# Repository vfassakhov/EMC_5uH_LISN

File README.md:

# 5µH LISN(Line Impedance Stabilization Network)

Open Source Hardware Dual 5µH DC LISN with 10dB Attenuator and Transient Limiter for Spectrum Analyzer EMC work.

A LISN is a [Line Impedance Stabilization Network](https://en.wikipedia.org/wiki/Line_Impedance_Stabilization_Network) used in conducted emissions testing.

The AIM of this Dual LISN is to be used for EMC pre-testing with frequency range 30kHz(or lower) to 110MHz(or up to 150MHz or more).

Fork from the [original project](https://github.com/bvernoux/EMC_5uH_LISN), the main changes are made the following:

* Convert project to [KiCad 8.0](https://www.kicad.org) version
* Added [KiBot](https://github.com/INTI-CMNB/KiBot) configuration, for automated generation of the documentation
* Improvement in this design: 
  * Replace Keystone 575-8 by screwed type Chinese alternative
  * Inductors are replaced by more affordable (need to make some tests)
  * BOM changes for cheaper Chinese alternatives
  * Another case (Gainta) is chosen

This work is heavily based on work from others mainly **Jay_Diddy_B** & **Noy** from EEVBLOG forum.

See all links related to the original Dual 5µH LISN:
* https://www.eevblog.com/forum/projects/5uh-lisn-for-spectrum-analyzer-emcemi-work/75/
* https://www.eevblog.com/forum/projects/5uh-lisn-for-spectrum-analyzer-emcemi-work/msg3420102/#msg3420102

Video related to EMC Conducted Emissions / LISN:
* Rohde Schwarz video Understanding LISNs: 
  * This video explains the design and function of a LISN (line impedance stabilization network) and how LISNs are used in conducted EMC testing.
  * https://www.youtube.com/watch?v=QPJzp66Yvzs
* EMC Conducted Emissions: How to connect and set up a LISN:
  * In this video Dr. Ali Shirsavar shows how you can connect and set up a LISN ready for pre-compliance testing of EMC conducted emissions.
  * https://www.youtube.com/watch?v=28oDdL9RnWM

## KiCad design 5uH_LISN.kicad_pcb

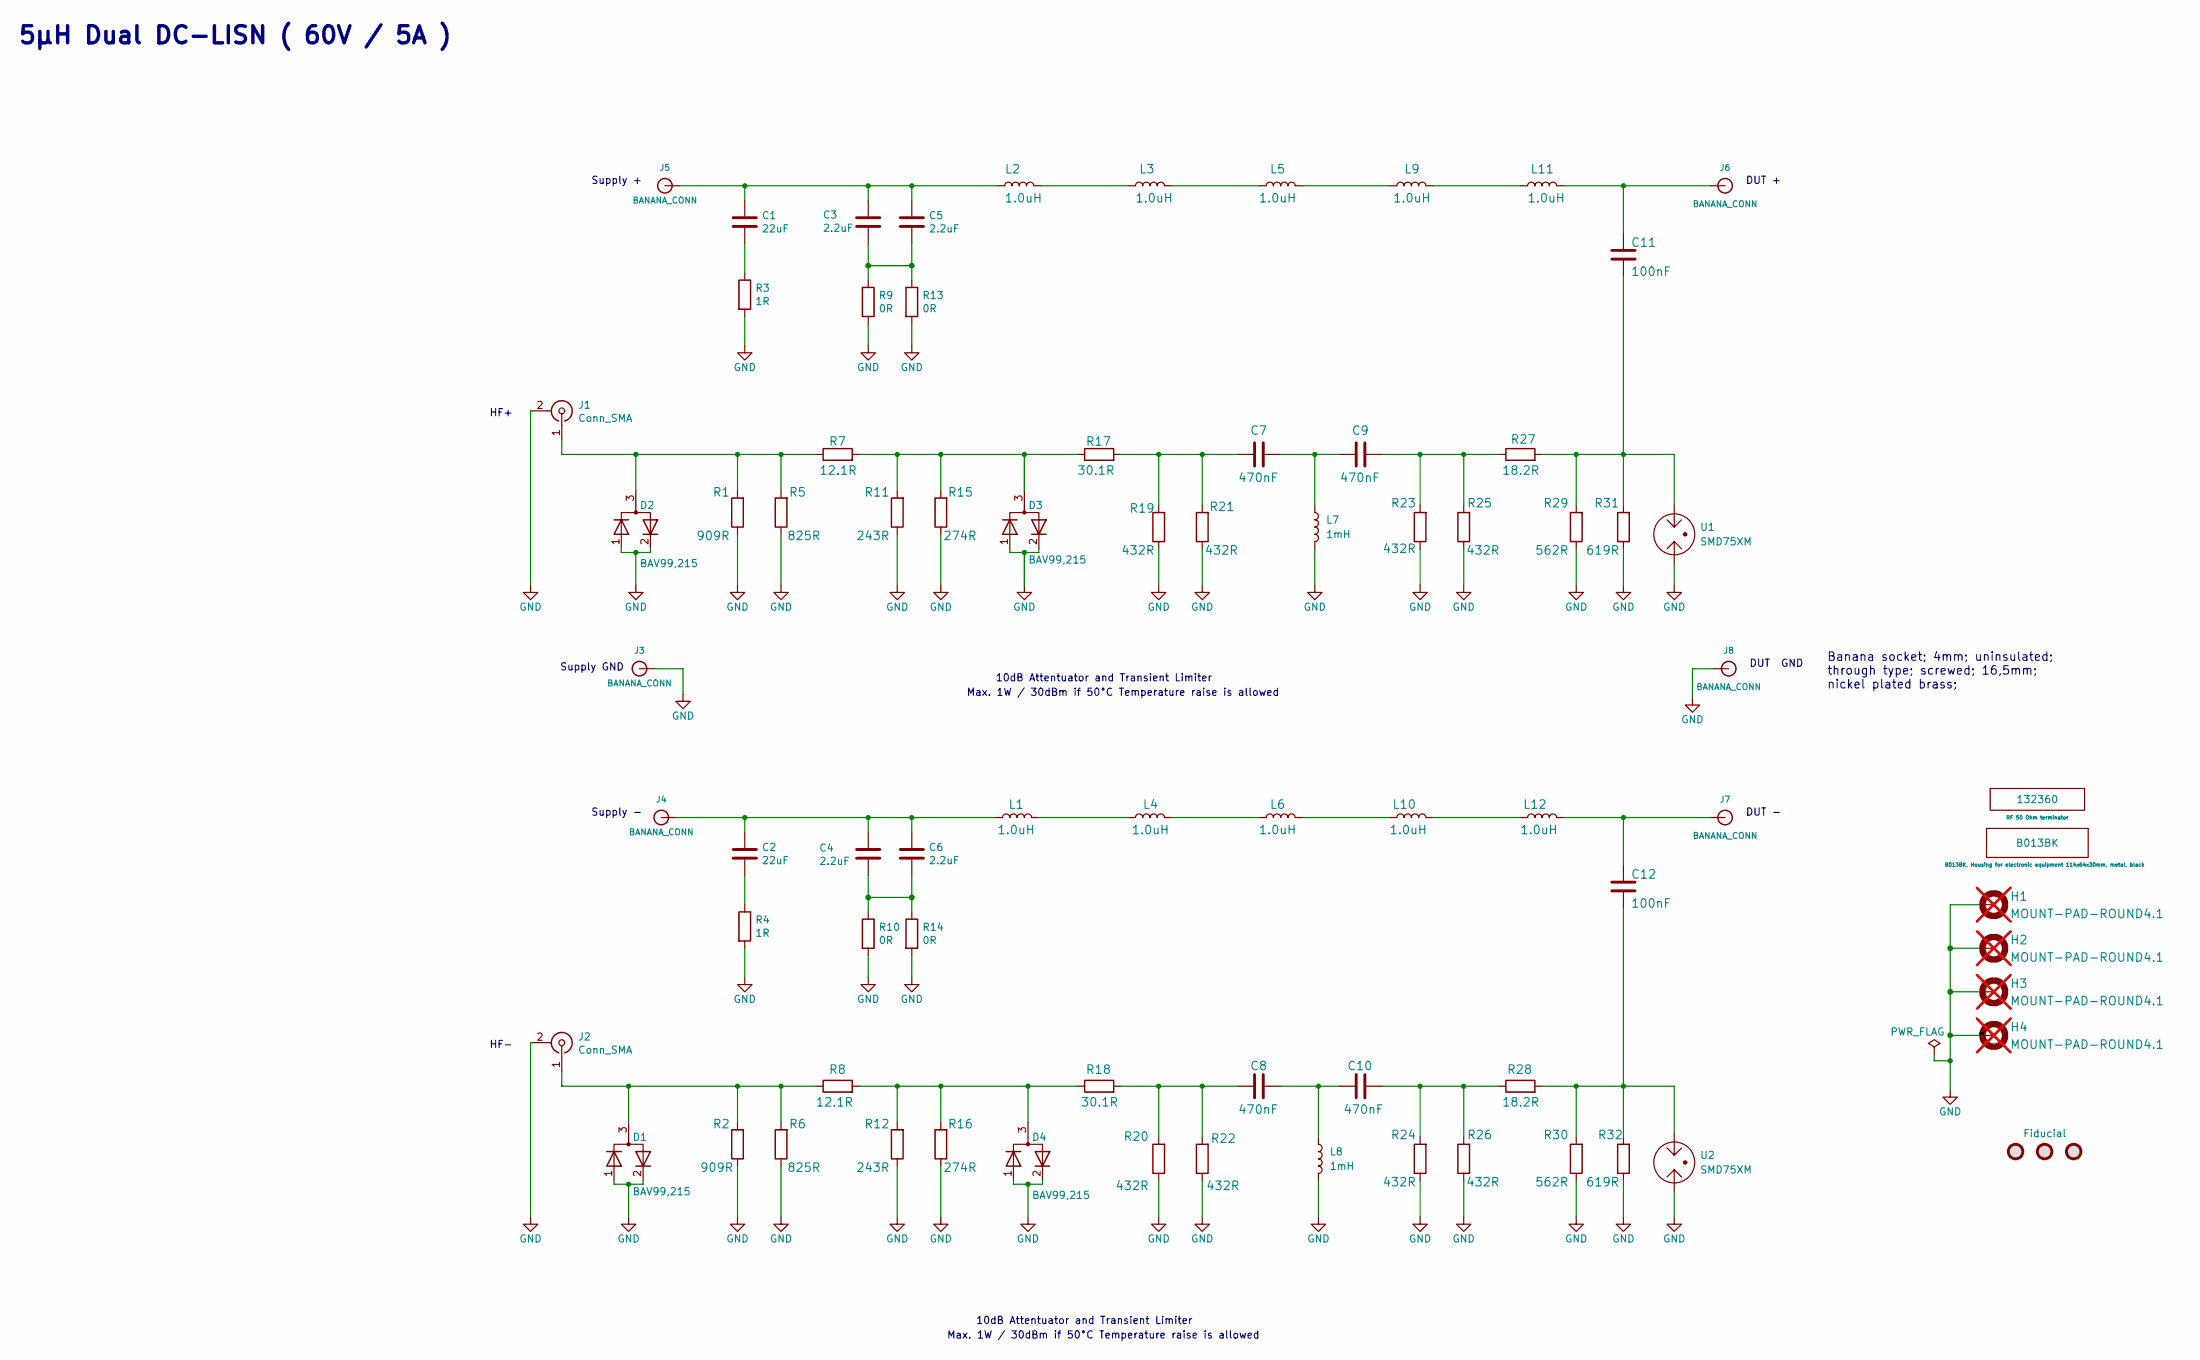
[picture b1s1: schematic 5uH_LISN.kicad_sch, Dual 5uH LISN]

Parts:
C1, C2: 22uF; C_2220_5650Metric; Part number KRM55WR72A226MH01L
C3, C4, C5, C6: 2.2uF; C_1210_3225Metric; Part number CC1210KKX7R0BB225
C7, C8, C9, C10: 470nF; C_0805_2012Metric; Part number CC0805KKX7R0BB474
C11, C12: 100nF; C_1206_3216Metric; Part number CC1206KKX7RYBB104
CASE1: B013BK; Part number B013BK
D1, D2, D3, D4: BAV99,215; SOT23-DIODEDUAL; Part number BAV99,215
FID1, FID2, FID3: Fiducial; Fiducial_1mm_Mask2mm
H1, H2, H3, H4: MOUNT-PAD-ROUND4.1; 4,1-PAD; not fitted
J1, J2: Conn_SMA; SMB_Jack_Vertical; Part number KLS1-SMA001
J3, J4, J5, J6, J7, J8: BANANA_CONN; 6,1-PAD; Part number 28.230
L1, L2, L3, L4, L5, L6, L9, L10, L11, L12: 1.0uH; SMS1040; Part number SMS1040-1R0MT
L7, L8: 1mH; L_1210_3225Metric; Part number NLFV32T-102K-EF
R1, R2: 909R; R_0805_2012Metric; Part number PTFR0805B909RP9
R3, R4: 1R; R_1218_3246Metric; Part number RC1218FK-071RL
R5, R6: 825R; R_0805_2012Metric; Part number RT0805BRD07825RL
R7, R8: 12.1R; R_1206_3216Metric; Part number RT1206BRD0712R1L
R9, R10, R13, R14: 0R; R_1206_3216Metric; Part number RC1206JR-7W0RL
R11, R12: 243R; R_0805_2012Metric; Part number RT0805BRD07243RL
R15, R16: 274R; R_0805_2012Metric; Part number RT0805BRD07274RL
R17, R18: 30.1R; R_1206_3216Metric; Part number AR06DTDV30R1
R19, R20, R21, R22, R23, R24, R25, R26: 432R; R_0805_2012Metric; Part number RT0805BRD07432RL
R27, R28: 18.2R; R_1206_3216Metric; Part number RT1206BRD0718R2L
R29, R30: 562R; R_0805_2012Metric; Part number RT0805BRD07562RL
R31, R32: 619R; R_0805_2012Metric; Part number RT0805BRE07619RL
RF1: 132360; RF_CAP; Part number 132360
U1, U2: SMD75XM; Fuse_1812_4532Metric; Part number SMD75XM

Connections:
GND: D1.1 (K), D1.2 (K), D2.1 (K), D2.2 (K), D3.1 (K), D3.2 (K), D4.1 (K), D4.2 (K), H1.B4,1 (MOUNT), H2.B4,1 (MOUNT), H3.B4,1 (MOUNT), H4.B4,1 (MOUNT), J1.2 (Ext), J2.2 (Ext), J3.1, J8.1, L7.2, L8.2, R1.1, R2.1, R3.2, R4.2, R5.1, R6.1, R9.2, R10.2, R11.1, R12.1, R13.2, R14.2, R15.1, R16.1, R19.1, R20.1, R21.1, R22.1, R23.1, R24.1, R25.1, R26.1, R29.1, R30.1, R31.1, R32.1, U1.1, U2.1
unnamed: C1.2, R3.1
unnamed: C2.2, R4.1
unnamed: C3.2, C5.2, R9.1, R13.1
unnamed: C4.2, C6.2, R10.1, R14.1
unnamed: C7.1, R17.2, R19.2, R21.2
unnamed: C7.2, C9.1, L7.1
unnamed: C8.1, R18.2, R20.2, R22.2
unnamed: C9.2, R23.2, R25.2, R27.1
unnamed: C8.2, C10.1, L8.1
unnamed: C10.2, R24.2, R26.2, R28.1
unnamed: C11.2, R27.2, R29.2, R31.2, U1.2
unnamed: C12.2, R28.2, R30.2, R32.2, U2.2
unnamed: D1.3 (A), J2.1 (In), R2.2, R6.2, R8.1
unnamed: D2.3 (A), J1.1 (In), R1.2, R5.2, R7.1
unnamed: D3.3 (A), R7.2, R11.2, R15.2, R17.1
unnamed: D4.3 (A), R8.2, R12.2, R16.2, R18.1
unnamed: C2.1, C4.1, C6.1, J4.1, L1.1
unnamed: C1.1, C3.1, C5.1, J5.1, L2.1
unnamed: C11.1, J6.1, L11.2
unnamed: C12.1, J7.1, L12.2
unnamed: L1.2, L4.1
unnamed: L2.2, L3.1
unnamed: L3.2, L5.1
unnamed: L4.2, L6.1
unnamed: L5.2, L9.1
unnamed: L6.2, L10.1
unnamed: L10.2, L12.1
unnamed: L9.2, L11.1

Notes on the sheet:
10dB Attentuator and Transient Limiter
Supply -
Max. 1W / 30dBm if 50°C Temperature raise is allowed
5µH Dual DC-LISN ( 60V / 5A )
DUT +
Supply +
DUT GND
Banana socket; 4mm; uninsulated; through type; screwed; 16,5mm; nickel plated brass;
Supply GND
HF-
HF+
DUT -

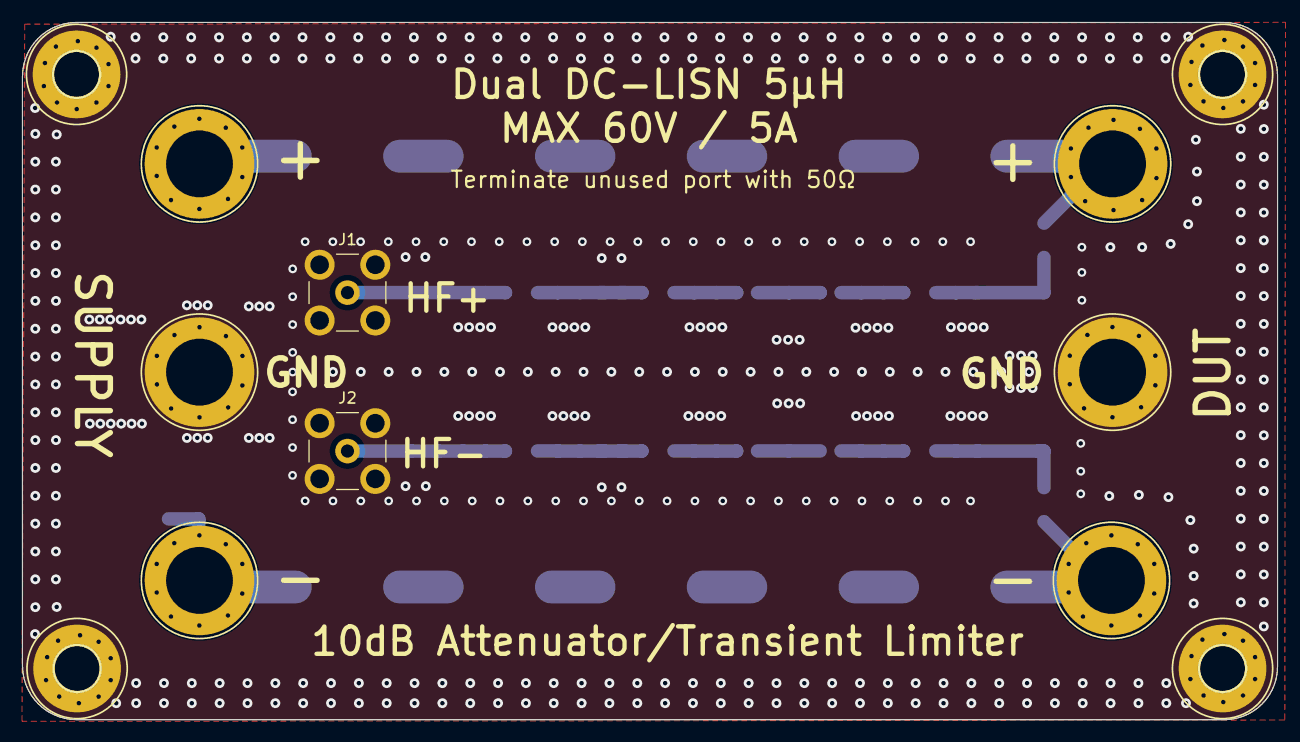
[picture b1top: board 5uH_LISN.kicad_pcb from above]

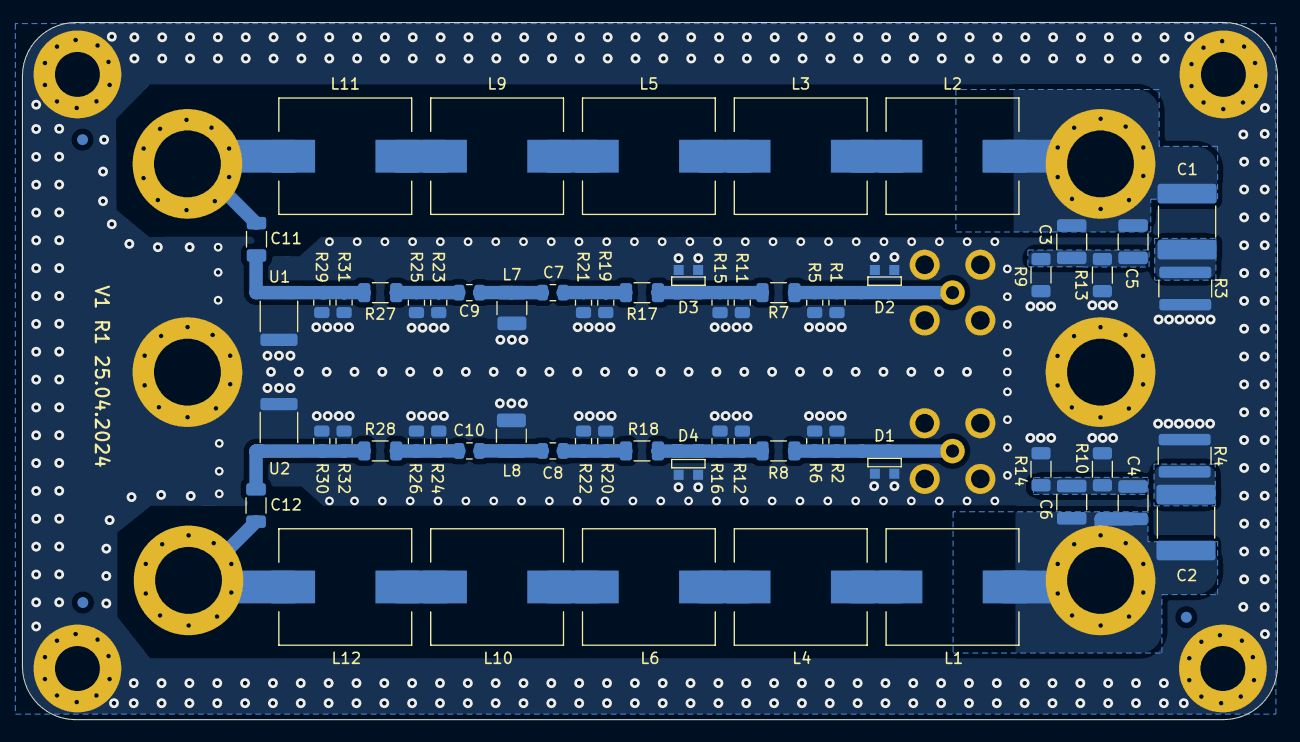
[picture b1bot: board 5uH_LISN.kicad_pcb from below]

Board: 2 copper layers, 114.5 x 63.6 mm, 79 parts (65 on the bottom side), 29 nets.

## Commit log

2024-04-29 redesign, see readme
